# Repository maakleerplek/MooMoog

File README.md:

# Compact D — two-board sloped synthesizer

**Documentation:** [**HTML docs**](https://maakleerplek.github.io/MooMoog/) (diagrams, port maps, schematics, 3D) ·
[Plan with block diagrams](docs/plan-r0.5.md) · [Architecture](hardware/split-r0.5/architecture.md) ·
[Remaining verification](hardware/split-r0.5/remaining-verification.md)

<table>
  <tr>
    <td width="50%"><br><sub><b>Rear</b> — audio jacks and USB ports</sub></td>
    <td width="50%"><br><sub><b>Exploded</b> — panel, control PCB, rails and electronics PCB</sub></td>
  </tr>
  <tr>
    <td width="50%"><br><sub><b>Interior</b> — sloped control board above the flat electronics board</sub></td>
    <td width="50%"><br><sub><b>Control PCB</b> — 19 pots, 8 encoders, 17 switches</sub></td>
  </tr>
</table>

<sub>Renders use reconstructed component models, not certified vendor CAD.</sub>

Active revision: [Split R0.5](hardware/split-r0.5/README.md).

A 220 × 150-mm control PCB under a 15° aluminium panel and a separate 210 × 90-mm electronics PCB, joined by a soldered 12-wire ribbon. CNC wooden sides, PMMA front/rear/bottom, classical printed knobs and the official maakleerplek wordmark. Panel screws now have dedicated clear borders.

- [Control PCB underside](hardware/split-r0.5/previews/control-pcb-underside.png)
- [Electronics PCB](hardware/split-r0.5/previews/electronics-pcb.png)
- [Control KiCad project](hardware/split-r0.5/control/control.kicad_pro)
- [Core KiCad project](hardware/split-r0.5/core/core.kicad_pro)
- [Electrical architecture and cable pinout](hardware/split-r0.5/architecture.md)
- [Enclosure and fabrication detail](mechanical/split-r0.5/README.md)
- [Laser engraving](mechanical/split-r0.5/panel-engraving-paths.svg)
- [Full CAD assembly](mechanical/split-r0.5/split-enclosure-and-boards.step)
- [Remaining verification](hardware/split-r0.5/remaining-verification.md)

Audio input removed. MCP internal contact pull-ups used. No added SMD packages on the carrier boards; purchased modules retain their factory SMD electronics. Current counts: 19 pots, 8 encoders, 17 switches and one power LED.

**Detailed design, not production-ready.** 53 known-pad connection trajectories are routed. Many final physical footprints are still unverified and their missing connections cannot be counted by DRC. Detailed renders use reconstructed component models, not certified vendor CAD. USB keyboard power from the ARCELI board remains unverified. No Gerbers or copper-milling release.

The [completion audit](hardware/split-r0.5/reports/completion-audit.json) compares the functional terminal list against actual KiCad pads: **246 required terminals currently lack matching pads, across 45 padless component instances**. These counts include functional module terminals whose physical mapping must still be established. Run `scripts/audit_completion_r05.py` with KiCad Python; it deliberately returns failure while completion blockers remain. A documented Same Sky SJ1-3523N candidate footprint is now available under `core/libraries/Documented.pretty`; it is **not yet installed on the active board**, because its board-edge and panel fit must be redesigned together.

Older revisions remain historical. The original specification is in `docs/projectspecification-v1.0.md`; decisions and user changes are in `docs/decisions.md`.

## Documentation workflow

- `docs/plan-r0.5.md` is the Markdown source of truth for the plan and the two block diagrams (GitHub renders the Mermaid).
- `docs/html/index.html` is the browsable copy, generated by `python3 scripts/build_docs_r05.py` (needs `mmdc` and `kicad-cli`). `docs/index.html` redirects to it.
- Pushing to `main` publishes `docs/html` to GitHub Pages through `.github/workflows/docs.yml` (one-time setup: Settings → Pages → Source: GitHub Actions).
- After a design change: rerun `scripts/build_schematics_r05.py`, then `scripts/build_docs_r05.py`, and commit the results.

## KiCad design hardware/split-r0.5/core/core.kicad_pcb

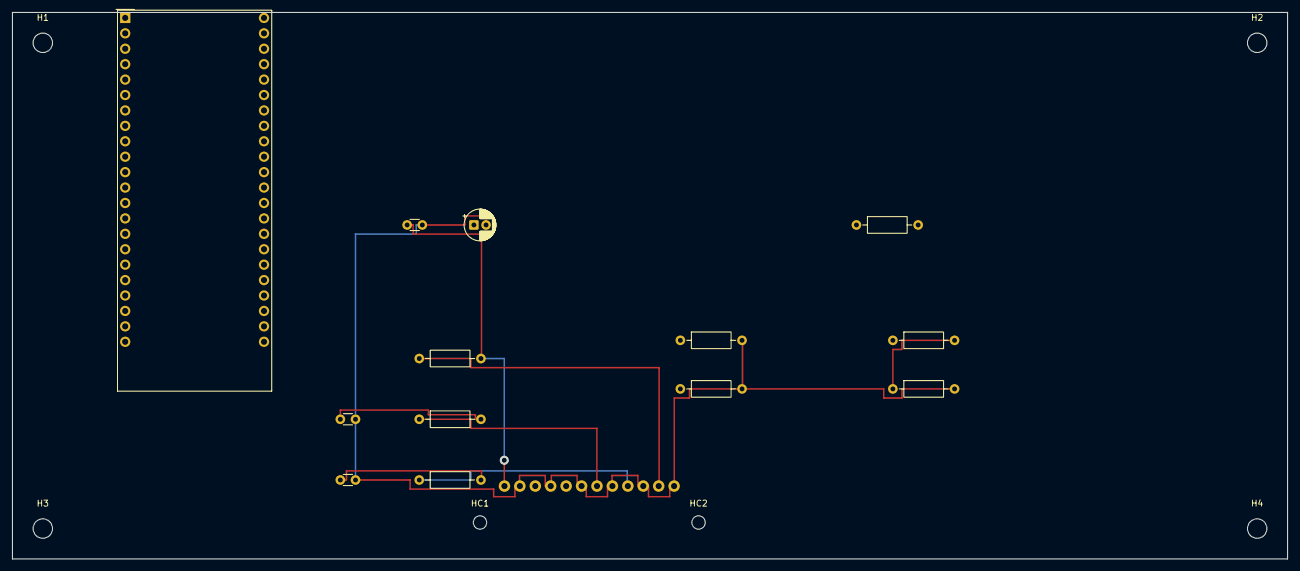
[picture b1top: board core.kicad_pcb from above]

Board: 2 copper layers, 210.0 x 90.0 mm, 23 parts (0 on the bottom side), 13 nets.

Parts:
CA1, CA2: 1nF; C_Disc_D3.0mm_W1.6mm_P2.50mm
CC1: 100nF; C_Disc_D3.0mm_W1.6mm_P2.50mm
CC2: 10uF 10V; CP_Radial_D5.0mm_P2.00mm
DAC1: PCM5102 / L main, R phones
H1, H2, H3, H4: MountingHole_3.2mm_M3
HC1, HC2: MountingHole_2.2mm_M2
HP1: Quystetes TPA6132 module
JCORE: 12-way soldered ribbon
JMAIN: 3.5mm MAIN output / MPN pending
MCU1: ARCELI ESP32-S3 N16R8; ESP32-S3-DevKitC-1_Module
RA1, RA2: 1k; R_Axial_DIN0207_L6.3mm_D2.5mm_P10.16mm_Horizontal
RA3: 100R; R_Axial_DIN0207_L6.3mm_D2.5mm_P10.16mm_Horizontal
RA4: 10k; R_Axial_DIN0207_L6.3mm_D2.5mm_P10.16mm_Horizontal
RA5: 4k7; R_Axial_DIN0207_L6.3mm_D2.5mm_P10.16mm_Horizontal
RA6, RA7: 100k; R_Axial_DIN0207_L6.3mm_D2.5mm_P10.16mm_Horizontal
RP5: 10k; R_Axial_DIN0207_L6.3mm_D2.5mm_P10.16mm_Horizontal

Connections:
3V3: CC1.1, JCORE.1, MCU1.3V3, RP5.2
DAC_MUTE_N: MCU1.GPIO41, RA6.1
GND: CA1.2, CA2.2, CC1.2, CC2.2, JCORE.2, JCORE.4, JCORE.6, JCORE.8, JCORE.10, JCORE.12, MCU1.GND, RA5.2, RA6.2, RA7.2
HP_EN: MCU1.GPIO40, RA7.1
HP_FEED: RA4.2, RA5.1
I2C_SCL: JCORE.5, MCU1.GPIO2
I2C_SDA: JCORE.3, MCU1.GPIO1
PANEL_IRQ: JCORE.11, MCU1.GPIO10, RP5.1
POT_ADC1: JCORE.7, RA1.1
POT_ADC1_FILTER: CA1.1, MCU1.GPIO4, RA1.2
POT_ADC2: JCORE.9, RA2.1
POT_ADC2_FILTER: CA2.1, MCU1.GPIO5, RA2.2
SYS_5V: CC2.1, MCU1.5V

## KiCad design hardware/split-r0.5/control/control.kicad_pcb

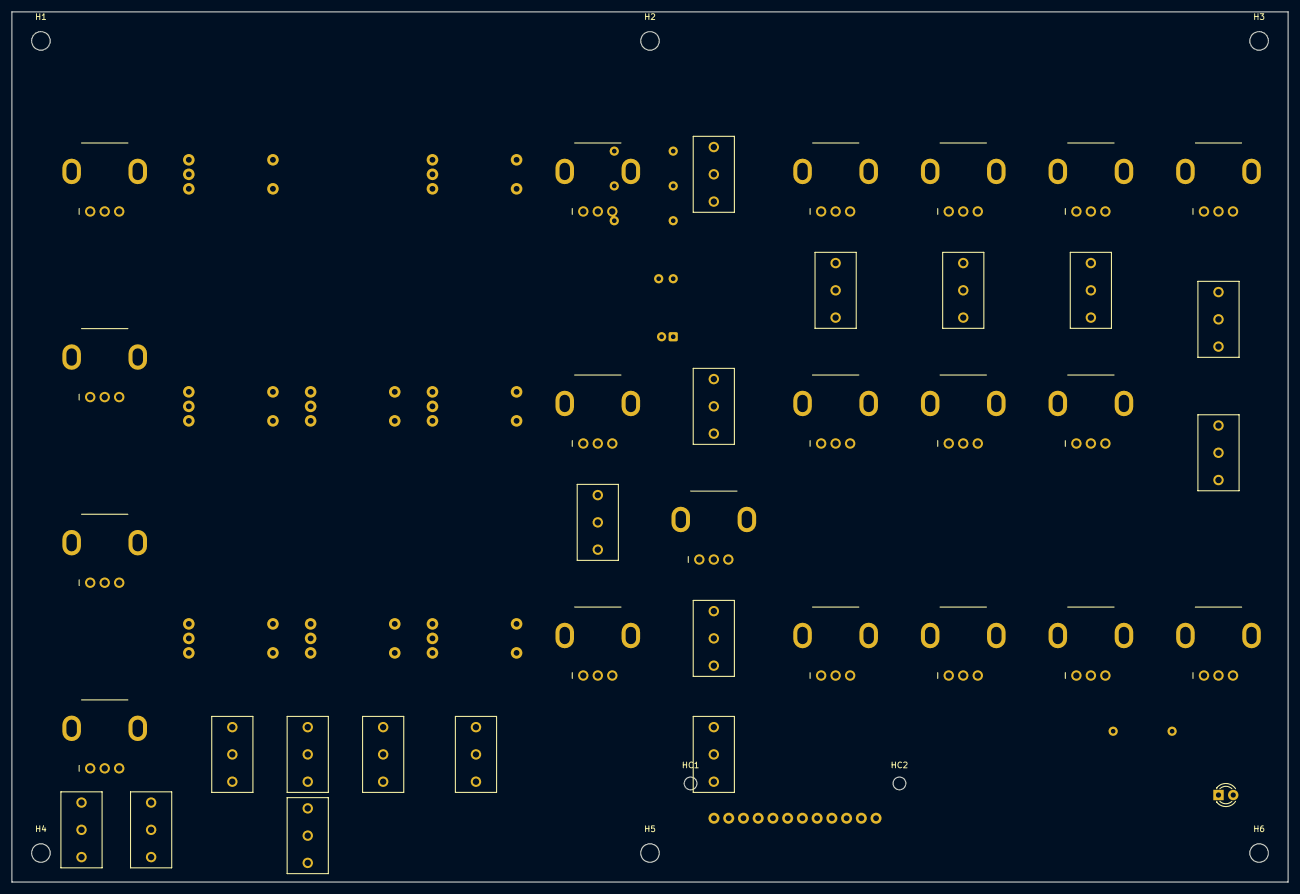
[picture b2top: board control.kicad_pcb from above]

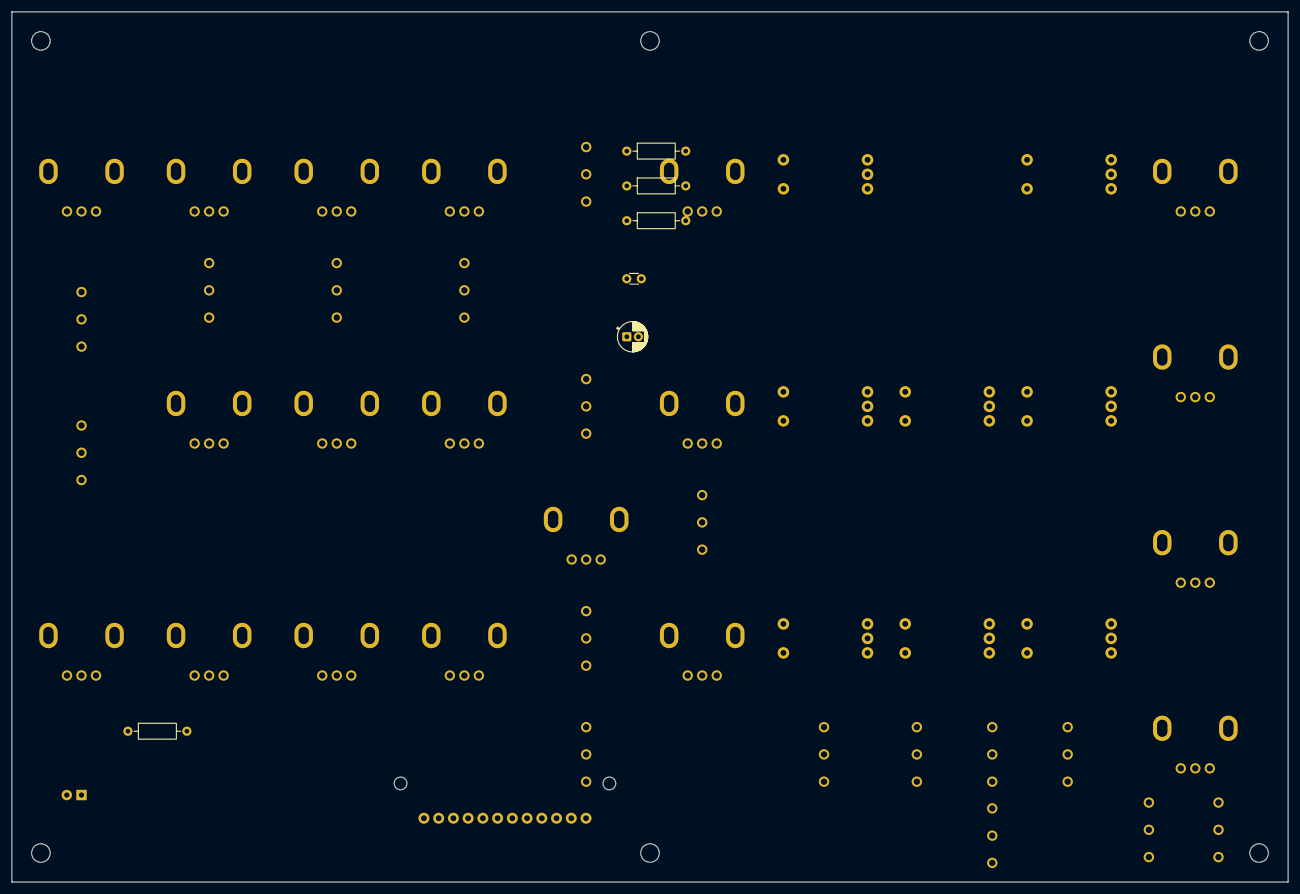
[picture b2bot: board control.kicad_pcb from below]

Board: 2 copper layers, 220.0 x 150.0 mm, 65 parts (12 on the bottom side), 5 nets, no tracks yet.

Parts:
CP1: 100nF; C_Disc_D3.0mm_W1.6mm_P2.50mm
CP2: 10uF 10V; CP_Radial_D5.0mm_P2.00mm
E1: EC11 RANGE; E1
E2: EC11 WAVEFORM; E2
E3: EC11 RANGE; E3
E4: EC11 FREQUENCY; E4
E5: EC11 WAVEFORM; E5
E6: EC11 RANGE; E6
E7: EC11 FREQUENCY; E7
E8: EC11 WAVEFORM; E8
H1, H2, H3, H4, H5, H6: MountingHole_3.2mm_M3
HC1, HC2: MountingHole_2.2mm_M2
IO1: MCP23017 module / 0x20
IO2: MCP23017 module / 0x21
IO3: MCP23017 module / 0x22
JPANEL: 12-way soldered ribbon
LED2: Power LED; LED_D3.0mm
MX1, MX2: CD74HC4067 module
RP1: 1k; R_Axial_DIN0207_L6.3mm_D2.5mm_P10.16mm_Horizontal
RP2: 10k; R_Axial_DIN0207_L6.3mm_D2.5mm_P10.16mm_Horizontal
RP3, RP4: 2k2 DNP; R_Axial_DIN0207_L6.3mm_D2.5mm_P10.16mm_Horizontal
RV1: RK097N B10K TUNE; Pot_B10K_RD901F_Vertical
RV2: RK097N B10K GLIDE; Pot_B10K_RD901F_Vertical
RV3: RK097N B10K MODULATION MIX; Pot_B10K_RD901F_Vertical
RV4: RK097N B10K LFO RATE; Pot_B10K_RD901F_Vertical
RV5, RV6, RV7, RV19: RK097N B10K VOLUME; Pot_B10K_RD901F_Vertical
RV9: RK097N B10K NOISE VOLUME; Pot_B10K_RD901F_Vertical
RV10: RK097N B10K CUTOFF FREQUENCY; Pot_B10K_RD901F_Vertical
RV11: RK097N B10K EMPHASIS; Pot_B10K_RD901F_Vertical
RV12: RK097N B10K AMOUNT OF CONTOUR; Pot_B10K_RD901F_Vertical
RV13, RV16: RK097N B10K ATTACK TIME; Pot_B10K_RD901F_Vertical
RV14, RV17: RK097N B10K DECAY TIME; Pot_B10K_RD901F_Vertical
RV15, RV18: RK097N B10K SUSTAIN LEVEL; Pot_B10K_RD901F_Vertical
RV20: RK097N B10K PHONES; Pot_B10K_RD901F_Vertical
S1: Osc mod; SS12D10_Slide_3P_P4.7
S2: Osc3 / EG; SS12D10_Slide_3P_P4.7
S3: Noise / LFO; SS12D10_Slide_3P_P4.7
S4: Glide on; SS12D10_Slide_3P_P4.7
S5: Decay on; SS12D10_Slide_3P_P4.7
S6: LFO shape; SS12D10_Slide_3P_P4.7
S7: Osc3 keyboard; SS12D10_Slide_3P_P4.7
S8: Osc 1 on; SS12D10_Slide_3P_P4.7
S9: Osc 2 on; SS12D10_Slide_3P_P4.7
S10: Osc 3 on; SS12D10_Slide_3P_P4.7
S12: Noise on; SS12D10_Slide_3P_P4.7
S13: White / Pink; SS12D10_Slide_3P_P4.7
S14: Filter mod; SS12D10_Slide_3P_P4.7
S15: Keytrack 1; SS12D10_Slide_3P_P4.7
S16: Keytrack 2; SS12D10_Slide_3P_P4.7
S17: Main on; SS12D10_Slide_3P_P4.7
S18: A-440; SS12D10_Slide_3P_P4.7

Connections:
3V3: CP1.1, CP2.1, JPANEL.1, LED2.2, RP2.2, RP3.2, RP4.2, RV1.3, RV2.3, RV3.3, RV4.3, RV5.3, RV6.3, RV7.3, RV9.3, RV10.3, RV11.3, RV12.3, RV13.3, RV14.3, RV15.3, RV16.3, RV17.3, RV18.3, RV19.3, RV20.3
GND: CP1.2, CP2.2, E1.C, E1.SW2, E2.C, E2.SW2, E3.C, E3.SW2, E4.C, E4.SW2, E5.C, E5.SW2, E6.C, E6.SW2, E7.C, E7.SW2, E8.C, E8.SW2, JPANEL.2, JPANEL.4, JPANEL.6, JPANEL.8, JPANEL.10, JPANEL.12, RP1.2, RV1.1, RV2.1, RV3.1, RV4.1, RV5.1, RV6.1, RV7.1, RV9.1, RV10.1, RV11.1, RV12.1, RV13.1, RV14.1, RV15.1, RV16.1, RV17.1, RV18.1, RV19.1, RV20.1, S1.2, S2.2, S3.2, S4.2, S5.2, S6.2, S7.2, S8.2, S9.2, S10.2, S12.2, S13.2, S14.2, S15.2, S16.2, S17.2, S18.2
I2C_SCL: JPANEL.5, RP4.1
I2C_SDA: JPANEL.3, RP3.1
PWR_LED: LED2.1, RP1.1

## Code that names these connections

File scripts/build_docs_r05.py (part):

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                 [(s['ref'], f"{s['label']} ({s['param']})", s['ref'] + '_ON', next(f"{x['module']}.{x['port']}" for x in SCAN if x['control'] == s['ref'])) for s in D['switches']])
    t_io = table(['Module', 'I²C address', 'Strap A0 / A1 / A2', 'GPA7 / GPB7 outputs'],
                 [('IO1', '0x20', 'GND / GND / GND', 'MUX_S0 / MUX_S1'), ('IO2', '0x21', '3V3 / GND / GND', 'MUX_S2 / MUX_S3'), ('IO3', '0x22', 'GND / 3V3 / GND', 'unused (low)')])
    t_rib = table(['Wire', 'Net', 'Role'], [(1, '3V3', 'control board supply'), (2, 'GND', 'return'), (3, 'I2C_SDA', 'ESP GPIO1 ↔ MCP SDA'), (4, 'GND', 'return'),
                  (5, 'I2C_SCL', 'ESP GPIO2 ↔ MCP SCL'), (6, 'GND', 'return'), (7, 'POT_ADC1', 'MX1 SIG → filter → GPIO4'), (8, 'GND', 'return'),
                  (9, 'POT_ADC2', 'MX2 SIG → filter → GPIO5'), (10, 'GND', 'return'), (11, 'PANEL_IRQ', 'MCP INTA (wire-OR) → GPIO10'), (12, 'GND', 'return')])
    t_mcu = table(['ESP32-S3 pin', 'Net', 'Goes to', 'Direction'], [
        ('5V (USB)', 'SYS_5V', 'DAC VIN, CC2 bulk cap', 'power in from USB-UART port'), ('3V3', '3V3', 'ribbon 1, HP1 VCC, CC1', 'power out (module regulator)'),
        ('GPIO1', 'I2C_SDA', 'ribbon 3 → MCP SDA', 'I²C data'), ('GPIO2', 'I2C_SCL', 'ribbon 5 → MCP SCL', 'I²C clock'),
        ('GPIO4', 'POT_ADC1_FILTER', 'RA1/CA1 ← ribbon 7 ← MX1', 'ADC in'), ('GPIO5', 'POT_ADC2_FILTER', 'RA2/CA2 ← ribbon 9 ← MX2', 'ADC in'),
        ('GPIO10', 'PANEL_IRQ', 'ribbon 11 ← MCP INTA (RP5 pull-up)', 'interrupt in'), ('GPIO15', 'I2S_BCLK', 'DAC BCK', 'I²S out'),
        ('GPIO16', 'I2S_LRCLK', 'DAC LCK', 'I²S out'), ('GPIO17', 'I2S_TX', 'DAC DIN', 'I²S out'), ('GPIO40', 'HP_EN', 'HP1 CTRL (RA7 pull-down)', 'output'),
        ('GPIO41', 'DAC_MUTE_N', 'DAC XSMT (RA6 pull-down)', 'output'), ('native USB', '—', 'USB-MIDI keyboard (host mode), power OPEN', 'USB host')])
    return t_pots, t_enc, t_sw, t_io, t_rib, t_mcu


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<ol><li>ESP → DAC over I²S (GPIO15 BCLK, GPIO16 LRCLK, GPIO17 TX); PLL mode, I²S format.</li>
<li>DAC left → <code>MAIN_RAW</code> → RA3 100&nbsp;Ω → rear jack (tip and ring tied, sleeve GND).</li>
<li>DAC right → <code>PHONES_RAW</code> → RA4/RA5 divider → <code>HP_FEED</code> → TPA6132 inputs → the module's own headphone jack.</li>
<li>GPIO41 <code>DAC_MUTE_N</code> drives XSMT; GPIO40 <code>HP_EN</code> drives the amp CTRL. Both have 100&nbsp;kΩ pull-downs.</li></ol>

<h2 id="ribbon">4. Ribbon (JPANEL ↔ JCORE)</h2>
<p>Pin 1 to pin 1; both ends are identical.</p>{t_rib}
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
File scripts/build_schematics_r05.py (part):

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    sh.text('decoupling 100 nF + 10 uF', 112, 33, 1.27)
    vertical_two_pin(sh, 'Device', 'R', 'RP2', 165, 50, '3V3', 'IO_RESET')
    sh.text('MCP reset pull-up', 158, 33, 1.27)
    vertical_two_pin(sh, 'Device', 'R', 'RP3', 120, 100, '3V3', 'I2C_SDA', dnp=True)
    vertical_two_pin(sh, 'Device', 'R', 'RP4', 138, 100, '3V3', 'I2C_SCL', dnp=True)
    sh.text('optional I2C pull-ups (DNP)', 112, 83, 1.27)
    # power LED: 3V3 -> LED (anode up) -> RP1 -> GND
    led = sh.place(libsym('Device', 'LED'), 'LED2', 'Power LED', 175, 98, 90, ref_at=(179, 97), val_at=(179, 99.5))
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    rp1 = sh.place(libsym('Device', 'R'), 'RP1', '1k', 175, 116, 0, ref_at=(178, 114.5), val_at=(178, 117.5))
    sh.connect(led, '1', rp1, '1')
    kp = led.pin('1')
    sh.label('PWR_LED', kp['x'], kp['y'] + 5.08, (1, 0))
    sh.wire((kp['x'], kp['y']), (kp['x'], kp['y'] + 5.08))
    sh.stub(rp1, '2', 'GND')
    sh.text('power LED', 168, 83, 1.27)
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    sh.frame(10, 10, 150, 135, '1  Ribbon and rails', 'Mirror of the control ribbon, pin 1 to pin 1.')
    ribbon(sh, 'JCORE', 45, 68)
    vertical_two_pin(sh, 'Device', 'C', 'CC1', 85, 110, '3V3', 'GND')
    vertical_two_pin(sh, 'Device', 'C_Polarized', 'CC2', 105, 110, 'SYS_5V', 'GND')
    sh.text('3V3 decoupling / 5 V bulk', 78, 92, 1.27)
    vertical_two_pin(sh, 'Device', 'R', 'RP5', 130, 110, '3V3', 'PANEL_IRQ')
    sh.text('IRQ pull-up', 123, 92, 1.27)

    # 2. pot filters
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    left = ['VIN', 'GND', None, 'BCK', 'LCK', 'DIN', None, 'SCK', 'FMT', None, 'XSMT']
    right = ['OUTL', 'OUTR']
    module(sh, 'DAC1', left, right, 'PCM5102_DAC_module', w=30.48, x=480, y=85)
    vertical_two_pin(sh, 'Device', 'R', 'RA6', 440, 112, 'DAC_MUTE_N', 'GND')
    sh.text('mute default', 433, 92, 1.27)

    # 5. outputs
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    jx = p2['x'] + 5.08
    sh.wire((p2['x'], p2['y']), (jx, p2['y']))
    sh.wire((jx, p2['y']), (jx + 7.62, p2['y']))
    sh.label('HP_FEED', jx + 7.62, p2['y'], (1, 0))
    sh.junction(jx, p2['y'])
    ra5 = sh.place(libsym('Device', 'R'), 'RA5', '4k7', jx, p2['y'] + 8, 0, ref_at=(jx + 3, p2['y'] + 6.1), val_at=(jx + 3, p2['y'] + 9.9))
    sh.wire((jx, p2['y']), (ra5.pin('1')['x'], ra5.pin('1')['y']))
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    right = ['OUTL', 'OUTR']
    module(sh, 'HP1', left, right, 'TPA6132_headphone_module', w=30.48, x=360, y=228)
    sh.text('onboard 3.5 mm headphone jack', 330, 258, 1.27)
    vertical_two_pin(sh, 'Device', 'R', 'RA7', 470, 240, 'HP_EN', 'GND')
    sh.text('enable default', 463, 222, 1.27)
    return sh

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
